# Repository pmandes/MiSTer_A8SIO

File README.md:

# MiSTer_A8SIO
Adapter for the SIO port to connect peripheral devices of the 8-bit Atari to the MiSTer FPGA.

## Interactive BOM: ##

<p align="center"></p>

## Components ##

The following modules can be used to build an adapter without using SMD components:

- AMS 1117 3.3V stabiliser module
- 2 x 4ch level shifter module
- USB 3.0 Type A angled socket
- SIO socket

For basic functionality, one level shifter (mounted on J5/J6) and an LDO power supply module (mounted on J7/J8) are sufficient.

The MOTOR CTRL circuit for controlling the tape recorder is optional.

**To connect to MisterFPGA, you need a USB3.0 A data transfer cable (blue type A plugs on both sides).**

**The adapter can ONLY be connected to the User Port on the I/O daughter board.**

## Prototype ##

The prototype was tested with the following equipment:
- Atari 1050 Floppy disk drive
- FujiNet network adapter
- SDriveMAX drive emulator

## Changleog: ##

**1.2**
- fix: crossed lines from USB3 A-A cable

**1.1**
- prototype / not published
- 2 * 4ch level shifters modules instead of HW221
  
**1.0**
- initial project

## PCB ##
Please consider supporting my open projects and order PCBs here:
https://www.pcbway.com/project/shareproject/MiSTer_A8SIO_a2581e8f.html

## Resources ##
New SIO sockets can be purchased here:
http://sikorsoft.waw.pl/hardware/gniazda-sio/

3D printed SIO socket project:
https://www.thingiverse.com/thing:5176832

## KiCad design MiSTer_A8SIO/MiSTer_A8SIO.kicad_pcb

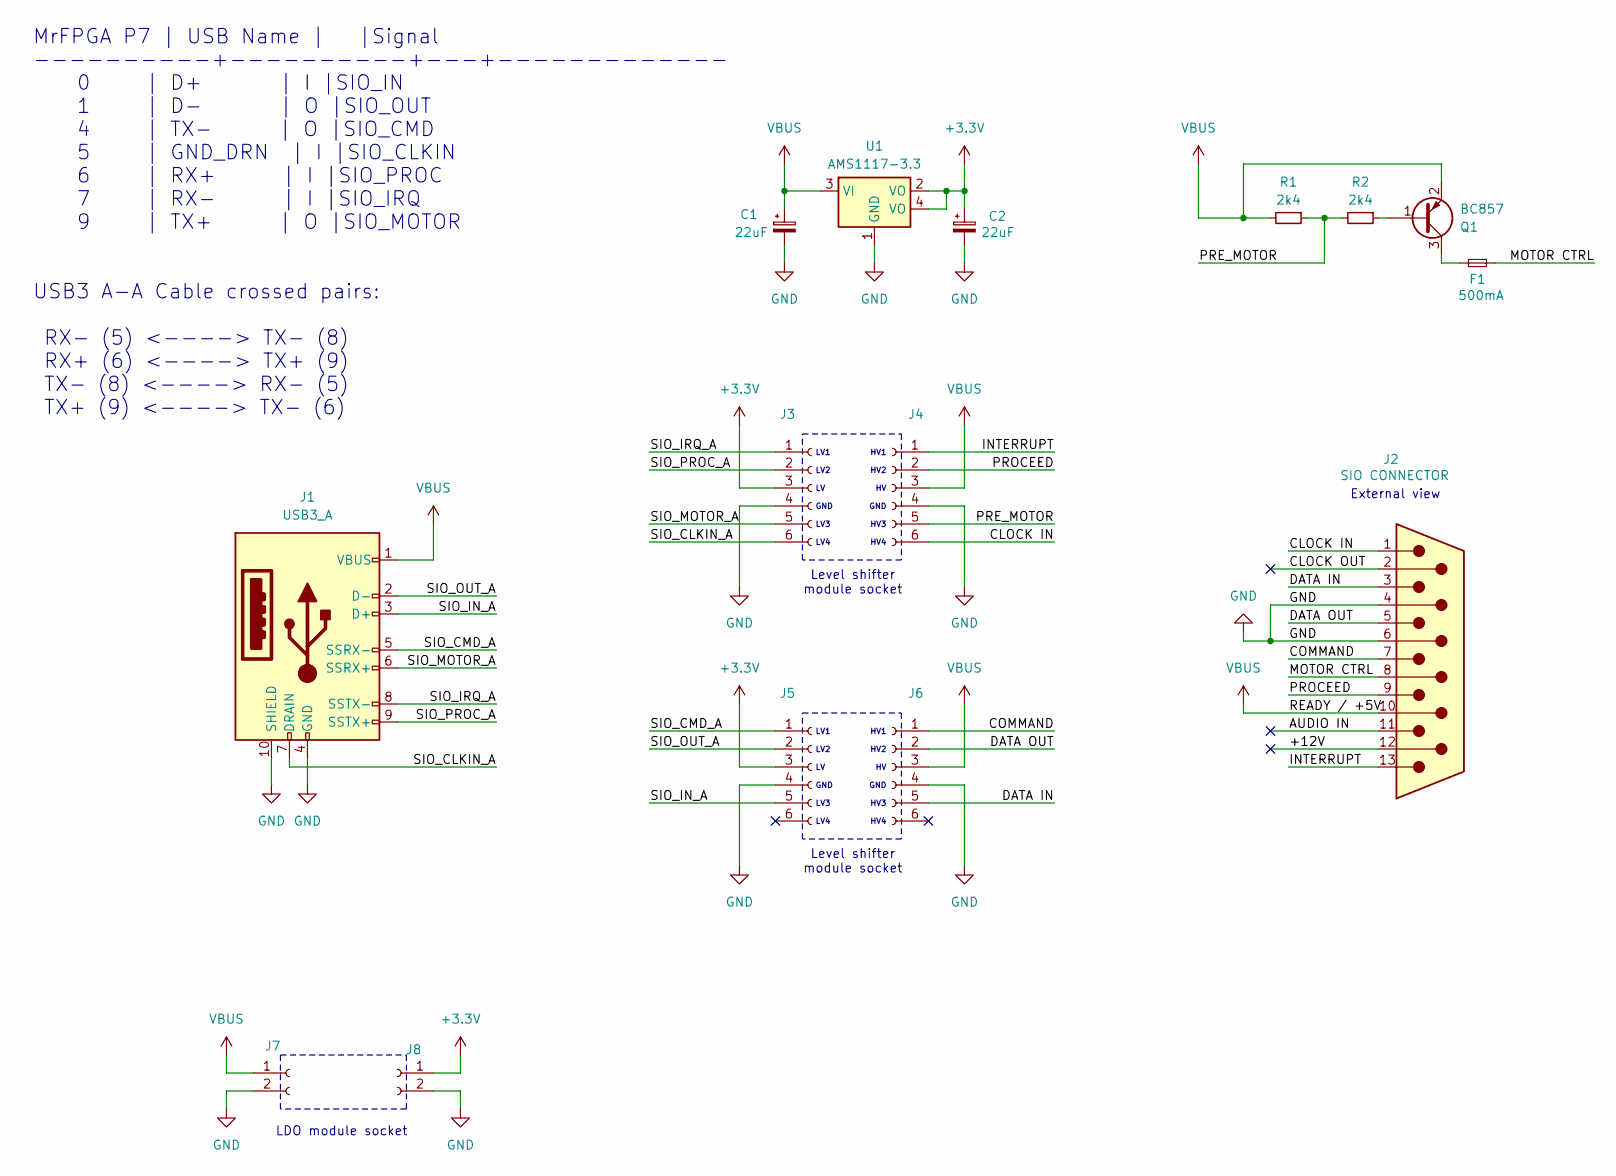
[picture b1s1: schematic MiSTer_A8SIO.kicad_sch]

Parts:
C1, C2: 22uF
F1: 500mA; Fuse_0805_2012Metric_Pad1.15x1.40mm_HandSolder
J1: USB3_A
J2: SIO CONNECTOR; SIO
J3, J4, J5, J6: Conn_01x06_Socket; PinHeader_1x06_P2.54mm_Vertical
J7, J8: Conn_01x02_Socket; PinHeader_1x02_P2.54mm_Vertical
Q1: BC857; SOT-23
R1, R2: 2k4; R_0805_2012Metric_Pad1.20x1.40mm_HandSolder
U1: AMS1117-3.3; SOT-223

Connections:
+3.3V: C2.1, J3.3, J5.3, J8.1, U1.2 (VO), U1.4 (VO)
/+12V: J2.12
/AUDIO IN: J2.11
/CLOCK IN: J2.1, J4.6
/CLOCK OUT: J2.2
/COMMAND: J2.7, J6.1
/DATA IN: J2.3, J6.5
/DATA OUT: J2.5, J6.2
/INTERRUPT: J2.13, J4.1
/MOTOR CTRL: F1.2, J2.8
/PRE_MOTOR: J4.5, R1.1, R2.2
/PROCEED: J2.9, J4.2
/SIO_CLKIN_A: J1.7 (DRAIN), J3.6
/SIO_CMD_A: J1.5 (SSRX-), J5.1
/SIO_IN_A: J1.3 (D+), J5.5
/SIO_IRQ_A: J1.8 (SSTX-), J3.1
/SIO_MOTOR_A: J1.6 (SSRX+), J3.5
/SIO_OUT_A: J1.2 (D-), J5.2
/SIO_PROC_A: J1.9 (SSTX+), J3.2
GND: C1.2, C2.2, J1.4 (GND), J1.10 (SHIELD), J2.4, J2.6, J3.4, J4.4, J5.4, J6.4, J7.2, J8.2, U1.1 (GND)
unnamed: Q1.1 (B), R2.1
unnamed: F1.1, Q1.3 (C)
VBUS: C1.1, J1.1 (VBUS), J2.10, J4.3, J6.3, J7.1, Q1.2 (E), R1.2, U1.3 (VI)

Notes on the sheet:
LDO module socket
External view
Level shifter module socket
HV1 HV2 HV GND HV3 HV4
LV1 LV2 LV GND LV3 LV4
MrFPGA P7 | USB Name | |Signal ----------+----------+---+------------- 0 | D+ | I |SIO_IN 1 | D- | O |SIO_OUT 4 | TX- | O |SIO_CMD 5 | GND_DRN | I |SIO_CLKIN 6 | RX+ | I |SIO_PROC 7 | RX- | I |SIO_IRQ 9 | TX+ | O |SIO_MOTOR USB3 A-A Cable crossed pairs: RX- (5) <----> TX- (8) RX+ (6) <----> TX+ (9)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

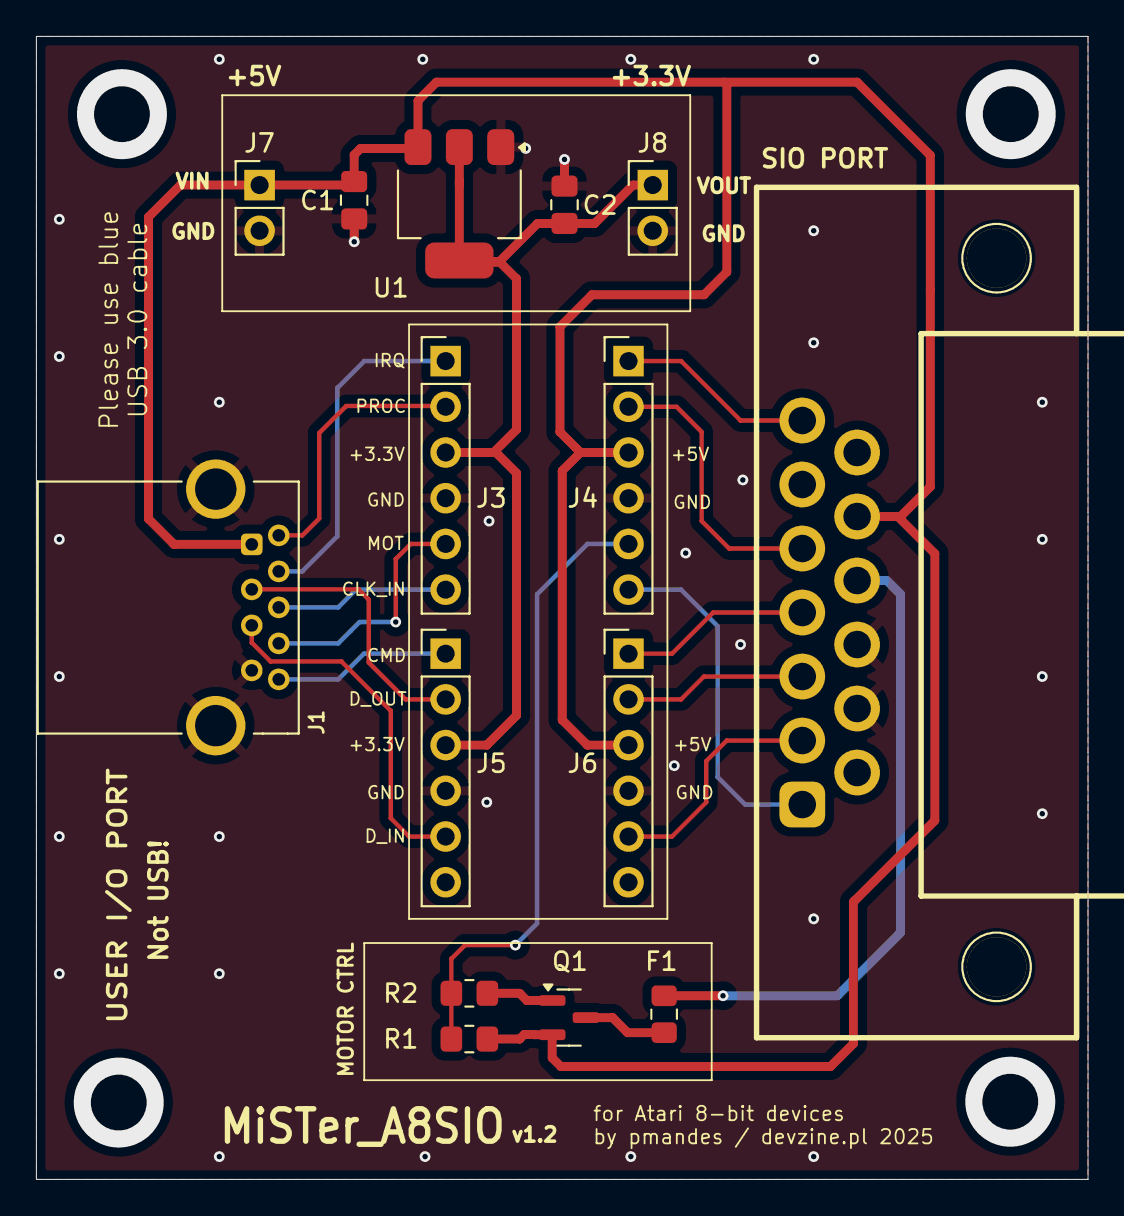
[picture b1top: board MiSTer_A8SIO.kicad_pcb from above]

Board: 2 copper layers, 58.4 x 63.5 mm, 15 parts (0 on the bottom side), 20 nets.

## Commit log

2025-01-25 KiCad project ver 1.0
2025-11-16 Ver. 1.2, Fixed crossed lines
2025-11-16 BOM image
2025-11-16 Update README with interactive BOM and changelog
    Added an interactive BOM section and changelog to README.
2025-11-17 Add components section to README
    Added components section to README with details on modules for building an adapter.
2025-11-17 Images for documentation.
2025-11-17 Update README with connection and prototype details
    Added information about USB3.0 A data transfer cable and prototype testing.
2025-11-17 Prototype images added.
2025-11-17 Update adapter connection instructions in README
    Clarified connection instructions for the adapter.
2025-11-17 Fix formatting of adapter connection instruction
2025-11-17 Add PCB support section to README
    Added a section for PCB support and ordering.
2025-11-17 PCB images added.
2025-11-17 Add images to README for enhanced visualization
    Added additional images to the README for better visualization.
2025-11-17 Update image layout in README.md
    Rearranged image display in README and added prototype images.
2025-11-18 Reorganize SIO sockets information in README
    Moved SIO sockets purchase link to Resources section.
2025-11-26 Add link to 3D printed SIO socket project
2026-04-21 3D printed housing
